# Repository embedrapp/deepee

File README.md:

# DeepEE

DeepEE is a small benchmark for AI agents doing embedded firmware and KiCad engineering. An agent receives a prompt plus starter files, edits a fresh working directory, and submits ordinary source files. An offline verifier checks the result. Conversation quality and screenshots do not count.

## Scope

Version 1.2 has 48 tasks: 12 in each engineering category.

| Category | Task IDs | Topics | Pass gate |
|---|---|---|---|
| Firmware | `deepee-fw-001`–`012` | I²C recovery; SHT3x, BME280, MCP9808, INA219, BMP280, ADS1115, DS18B20, SCD4x, PCA9685, and MAX31855 drivers; Modbus CRC | Protected API + native C tests + PlatformIO build |
| Code repair | `deepee-repair-001`–`012` | Scheduler rollover, ring buffers, ADC scaling, SLIP, MQTT, UTF-8, CBOR, PPP FCS, HTTP chunks, Base64, Modbus CRC, and wrap-safe tick timing | Protected API + native C tests |
| Schematics | `deepee-sch-001`–`012` | Power-input repair, MCP9808, INA219, ADS1115, BMP280, AP2112, USB-C sink, RS-485, CAN, I²C level shifting, microSD, and NE555 | Exact component/pin-net contract + exported netlist + ERC |
| PCB | `deepee-pcb-001`–`012` | nRF24L01, MCP9808, and the same ten researched interface circuits used by the schematic set | Exact footprint/pad/outline contract + fully routed nets + DRC |

The tasks are compact adaptations of real bug reports, open-source boards, official KiCad QA material, and published breakout use cases. Provenance is recorded in each task's `SOURCE.md` and summarized in [docs/TASK_SOURCES.md](docs/TASK_SOURCES.md).

The evaluation contract and its limits are documented in [docs/VALIDATION_MODEL.md](docs/VALIDATION_MODEL.md). Contributions must follow [CONTRIBUTING.md](CONTRIBUTING.md), including the known-good and mutant release gates.

## What is verified

Every task declares public, machine-readable critical requirements. A task score remains binary:

```text
all checks pass -> 1
anything fails  -> 0
```

The primary aggregate is Pass@1: the fraction of tasks passed on an agent's first publishable attempt. Score files also contain each requirement outcome, its engineering layer, leaf evidence, a layer-level score vector, and a stable decision hash. A strong result in one layer cannot mask a failed critical requirement in another.

The verifier checks required parts and pin/pad nets without comparing an entire design to golden geometry. KiCad performs the final ERC/DRC gate. PCB contracts additionally measure declared physical constraints directly from native copper: all named nets use at least 0.25 mm track width, and the USB-C repair constrains routed D+/D− skew to 1.0 mm. The release gate runs a targeted mutant for every critical requirement and must reject all of them.

This is deliberately a KiCad-native benchmark, not a tool-agnostic EDA benchmark. An AI system may be compared if it can produce the required native KiCad 10 artifacts. Altium- or EasyEDA-only outputs are out of scope because silently converting them would weaken the assurance and make the comparison misleading.

Firmware is verified by native behavioral tests and a real target build. Version 1.2 does not claim runtime peripheral, analog, thermal, EMI, or fabrication signoff; those require suitable simulation or hardware-in-the-loop fixtures and are excluded from task claims.

## Lightweight local preparation

No VM, Colima instance, Docker image, KiCad install, or PlatformIO install is needed on the development laptop. The repository checks use Python and a host C compiler only:

```bash
python3 -m venv .venv
. .venv/bin/activate
pip install -e .
make test
```

The Dockerfiles and scripts are deployment material for a later x86_64 Ubuntu EC2 run. They are not started by the commands above.

## EC2 execution

On an Ubuntu 24.04 x86_64 host:

```bash
./scripts/bootstrap-ec2-ubuntu.sh
# Log out and back in once for Docker group membership.
export CODEX_API_KEY='...'
./scripts/run-ec2-baseline.sh --all-tasks
```

For a ChatGPT subscription-authenticated Codex run, complete `codex login --device-auth` on the host and use `./scripts/run-ec2-chatgpt-baseline.sh` instead.

The deployment builds separate `deepee-agent:1.2.0` and `deepee-verifier:1.2.0` images. The agent image has KiCad 10.0.4, PlatformIO 6.1.19, compilers, and Codex but no benchmark tasks or verifier code. Agent runs use an internal-only Docker network and one explicit CONNECT-proxy profile: API-key runs permit `api.openai.com:443`, while ChatGPT-subscription runs additionally permit `auth.openai.com:443` and `chatgpt.com:443`. Both profiles block every other authority and direct internet egress, and the effective profile and allowlist are recorded in the run. Verification runs without any network or agent credentials. Before a baseline starts, the Ubuntu host also proves one private reference submission for every task against that same verifier image. See [docs/EC2.md](docs/EC2.md) and [docs/RUN_PROTOCOL.md](docs/RUN_PROTOCOL.md).

For a manual external agent that uses KiCad:

```bash
deepee benchmark \
  --agent agents/manual-kicad.yaml \
  --task deepee-pcb-001 \
  --prepare-only

deepee verify \
  --container-image deepee-verifier:1.2.0 \
  --task deepee-pcb-001 \
  --run-dir '<printed-run-directory>' \
  --output results/scored/external-pcb-run.json
```

DeepEE's original code and fixtures are MIT licensed. The KiCad-derived schematic starter identified in [THIRD_PARTY_NOTICES.md](THIRD_PARTY_NOTICES.md) retains its GPLv3 license. Compare leaderboard results only when the benchmark and task hashes match.

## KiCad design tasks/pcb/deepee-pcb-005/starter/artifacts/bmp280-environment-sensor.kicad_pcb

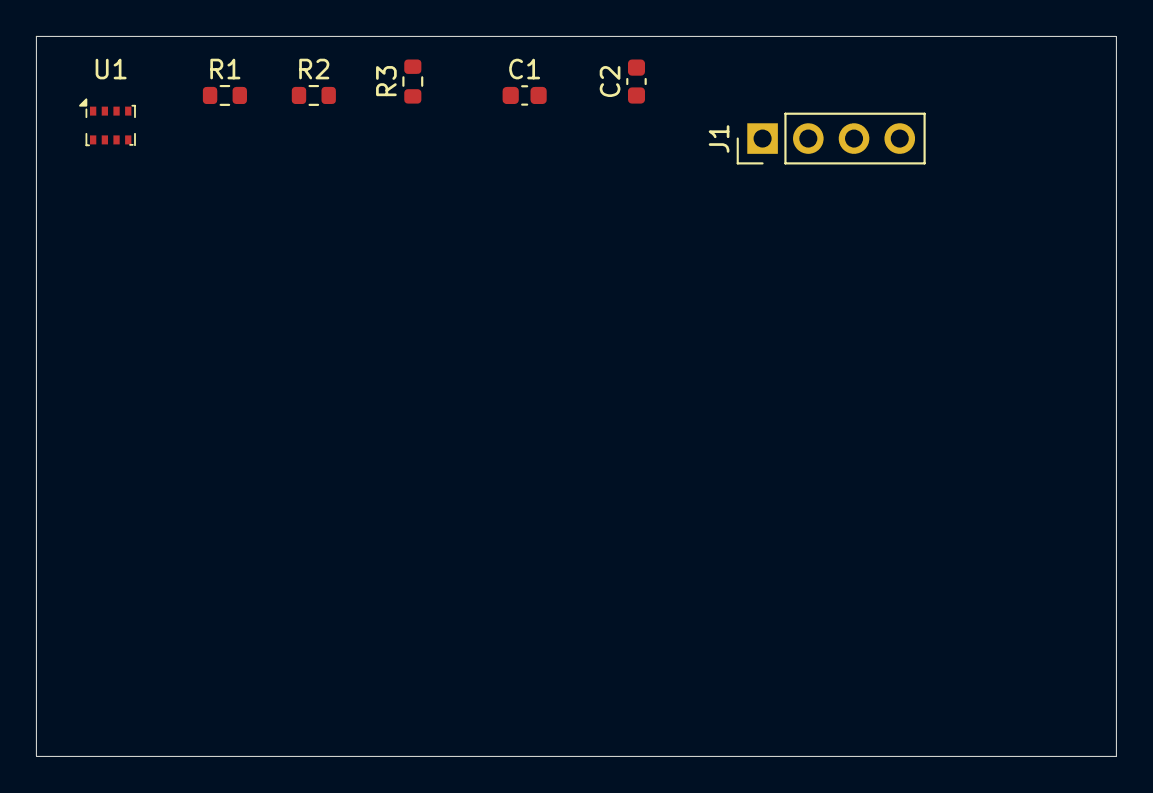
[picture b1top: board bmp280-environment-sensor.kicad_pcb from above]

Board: 2 copper layers, 60.0 x 40.0 mm, 7 parts (0 on the bottom side), 5 nets, no tracks yet.

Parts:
C1: 100nF; C_0603_1608Metric
C2: 1uF; C_0603_1608Metric
J1: Conn_01x04; PinHeader_1x04_P2.54mm_Vertical
R1, R2: 4.7k; R_0603_1608Metric
R3: 0R; R_0603_1608Metric
U1: BMP280; Bosch_LGA-8_2x2.5mm_P0.65mm_ClockwisePinNumbering

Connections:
3V3: C1.1, C2.1, J1.1, R1.1, R2.1, U1.2, U1.6, U1.8
ADDR: R3.1, U1.5
GND: C1.2, C2.2, J1.2, R3.2, U1.1, U1.7
SCL: J1.4, R2.2, U1.4
SDA: J1.3, R1.2, U1.3

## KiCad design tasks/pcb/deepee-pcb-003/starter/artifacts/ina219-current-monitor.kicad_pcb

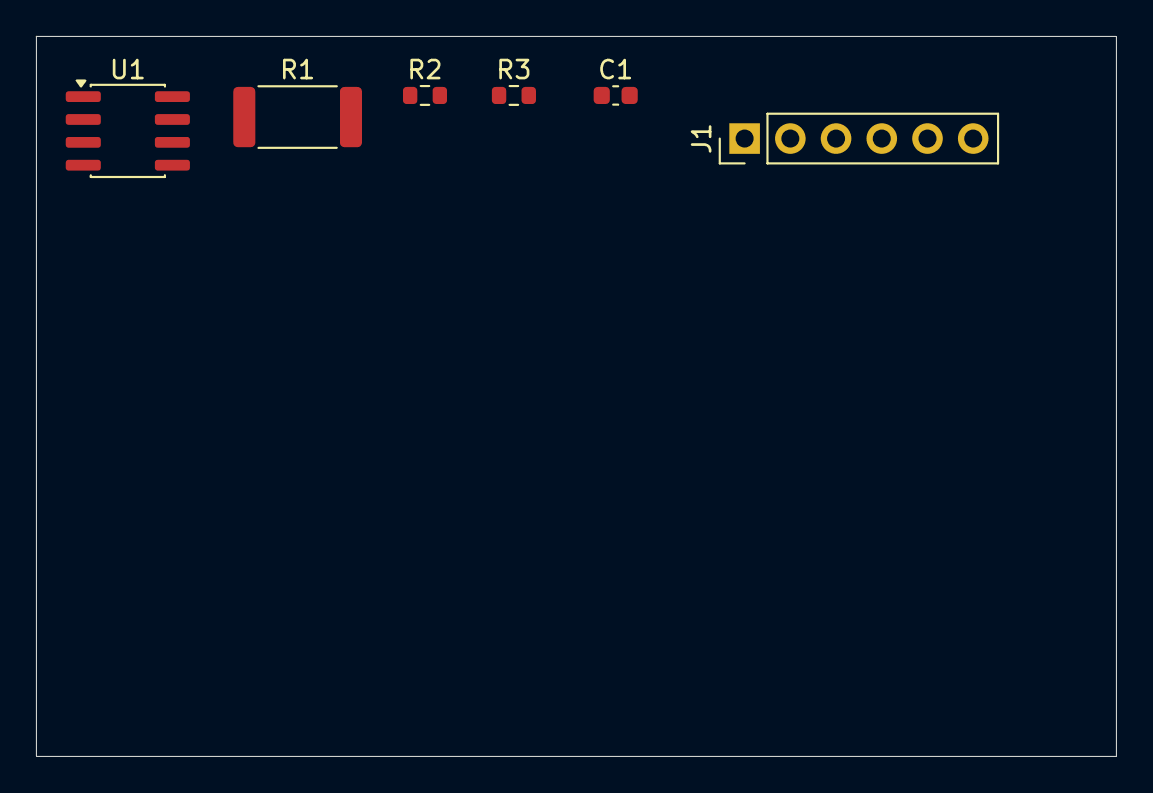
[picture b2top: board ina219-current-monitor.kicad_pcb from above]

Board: 2 copper layers, 60.0 x 40.0 mm, 6 parts (0 on the bottom side), 6 nets, no tracks yet.

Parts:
C1: 100nF; C_0603_1608Metric
J1: Conn_01x06; PinHeader_1x06_P2.54mm_Vertical
R1: 0.1R; R_2512_6332Metric
R2, R3: 4.7k; R_0603_1608Metric
U1: INA219AxD; SOIC-8_3.9x4.9mm_P1.27mm

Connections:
3V3: C1.1, J1.3, R2.1, R3.1, U1.5
GND: C1.2, J1.4, U1.1, U1.2, U1.6
SCL: J1.6, R3.2, U1.4
SDA: J1.5, R2.2, U1.3
VIN_IN: J1.1, R1.1, U1.8
VIN_OUT: J1.2, R1.2, U1.7

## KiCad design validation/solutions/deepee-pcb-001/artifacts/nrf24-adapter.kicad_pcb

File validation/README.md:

# Release validation

This directory contains one known-good submission for every benchmark task plus the validator-adequacy tooling. It is public for reproducibility but used only as a release gate: the validation harness overlays each solution onto a fresh starter and verifies it with the same offline, read-only submission mount used for real scores.

`validation/` is excluded from the Docker build context and is not copied into either benchmark image. It must never be mounted into an agent run. The CI and EC2 release gates run it only after the agent and verifier images have been built. Agent networking is restricted, so an evaluated agent cannot retrieve the public solutions during its run.

The adequacy gate creates one targeted mutant for every critical requirement and requires the mapped oracle to reject it:

```bash
python -m validation.adequacy --container-image deepee-verifier:1.2.0
```

This proves that the validator detects the declared fault. It does not prove that every possible engineering defect has been modeled; task claims must stay within the published requirement contract.

Regenerate the KiCad fixtures only when their task contracts change:

```bash
python -m pip install -r validation/requirements.txt
KICAD_SYMBOL_DIR=/usr/share/kicad/symbols \
  python validation/generate_hardware_fixtures.py

python validation/generate_expanded_code_tasks.py
KICAD_SYMBOL_DIR=/usr/share/kicad/symbols \
  python validation/generate_expanded_hardware_tasks.py

# Run with KiCad's Python runtime to replace the repair-board placeholders
# with placed, net-assigned library footprints.
KICAD_FOOTPRINT_DIR=/usr/share/kicad/footprints \
  python validation/generate_expanded_hardware_tasks.py --pcb-starters-only

# Inside the exact verifier image so pcbnew and the footprint libraries match:
python validation/canonicalize_hardware_boards.py adapter
python validation/canonicalize_hardware_boards.py breakout
```

Validate all reference submissions on the Ubuntu x86_64 benchmark host:

```bash
python -m validation.reference --container-image deepee-verifier:1.2.0
```

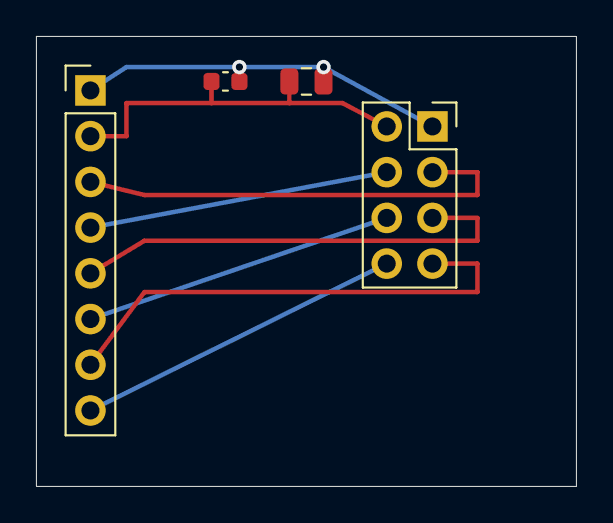
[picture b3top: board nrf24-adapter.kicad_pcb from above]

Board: 2 copper layers, 30.0 x 25.0 mm, 4 parts (0 on the bottom side), 8 nets.

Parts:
C1: 10uF; C_0805_2012Metric
C2: 100nF; C_0603_1608Metric
J1: Conn_01x08; PinHeader_1x08_P2.54mm_Vertical
J2: nRF24L01_Module; PinSocket_2x04_P2.54mm_Vertical

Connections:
+3V3: C1.1, C2.1, J1.2, J2.2
CE: J1.3, J2.3
CSN: J1.4, J2.4
GND: C1.2, C2.2, J1.1, J2.1
IRQ: J1.8, J2.8
MISO: J1.7, J2.7
MOSI: J1.6, J2.6
SCK: J1.5, J2.5

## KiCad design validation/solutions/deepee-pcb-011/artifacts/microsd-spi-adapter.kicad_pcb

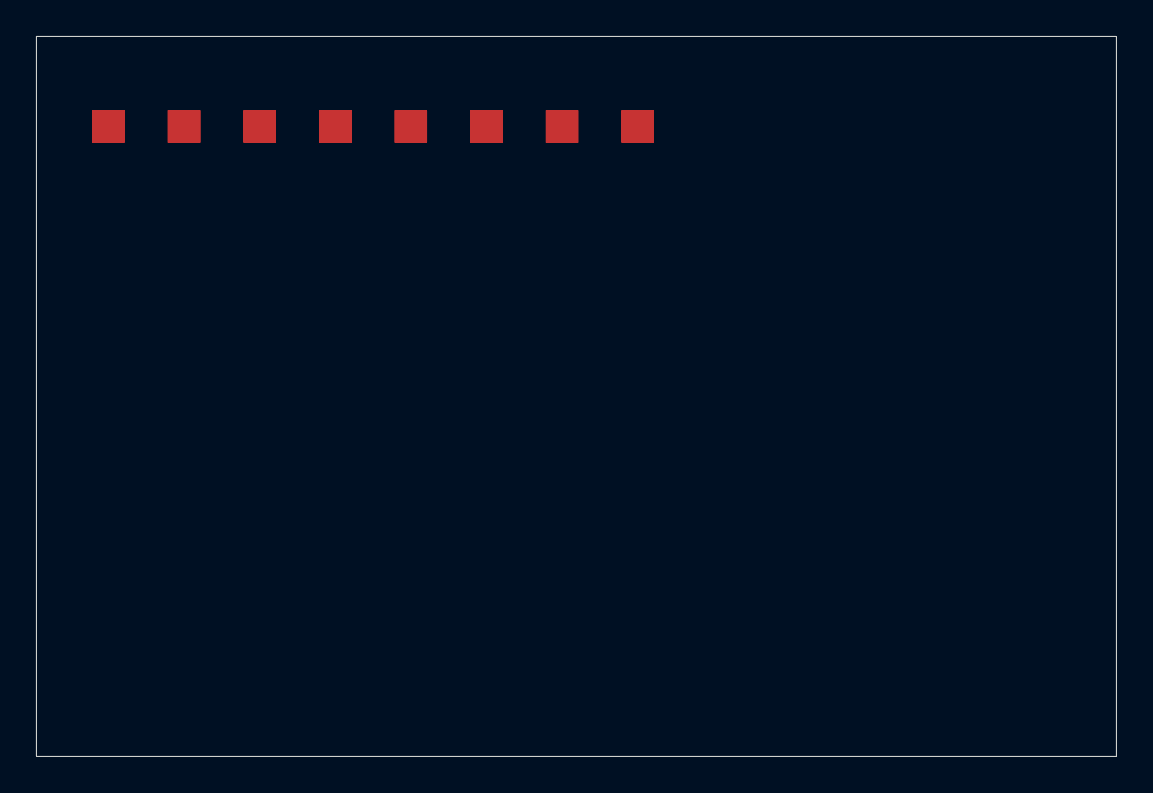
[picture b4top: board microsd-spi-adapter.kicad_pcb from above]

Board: 2 copper layers, 60.0 x 40.0 mm, 7 parts (0 on the bottom side), 8 nets.

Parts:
C1: 100nF; C_0603_1608Metric
C2: 10uF; C_0805_2012Metric
J1: Micro_SD_Card; microSD_HC_Hirose_DM3AT-SF-PEJM5
J2: Conn_01x06; PinHeader_1x06_P2.54mm_Vertical
R1, R2, R3: 47k; R_0603_1608Metric

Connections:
3V3: C1.1, C2.1, J1.4, J2.1, R1.1, R2.1, R3.1
DAT1: J1.8, R2.2
DAT2: J1.1, R3.2
GND: C1.2, C2.2, J1.6, J1.SH, J2.2
MISO: J1.7, J2.5
MOSI: J1.3, J2.4
SCK: J1.5, J2.6
SD_CS: J1.2, J2.3, R1.2

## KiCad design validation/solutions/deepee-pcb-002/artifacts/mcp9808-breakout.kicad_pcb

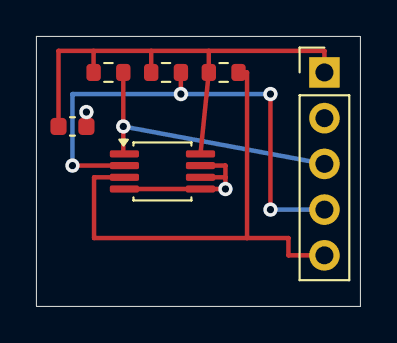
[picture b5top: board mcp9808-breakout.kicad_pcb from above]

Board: 2 copper layers, 18.0 x 15.0 mm, 6 parts (0 on the bottom side), 5 nets.

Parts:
C1: 100nF; C_0603_1608Metric
J1: Conn_01x05; PinHeader_1x05_P2.54mm_Vertical
R1, R2: 4.7k; R_0603_1608Metric
R3: 10k; R_0603_1608Metric
U1: MCP9808T-E/MS; MSOP-8_3x3mm_P0.65mm

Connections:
3V3: C1.1, J1.1, R1.1, R2.1, R3.1, U1.8
ALERT: J1.5, R3.2, U1.3
GND: C1.2, J1.2, U1.4, U1.5, U1.6, U1.7
SCL: J1.4, R2.2, U1.2
SDA: J1.3, R1.2, U1.1

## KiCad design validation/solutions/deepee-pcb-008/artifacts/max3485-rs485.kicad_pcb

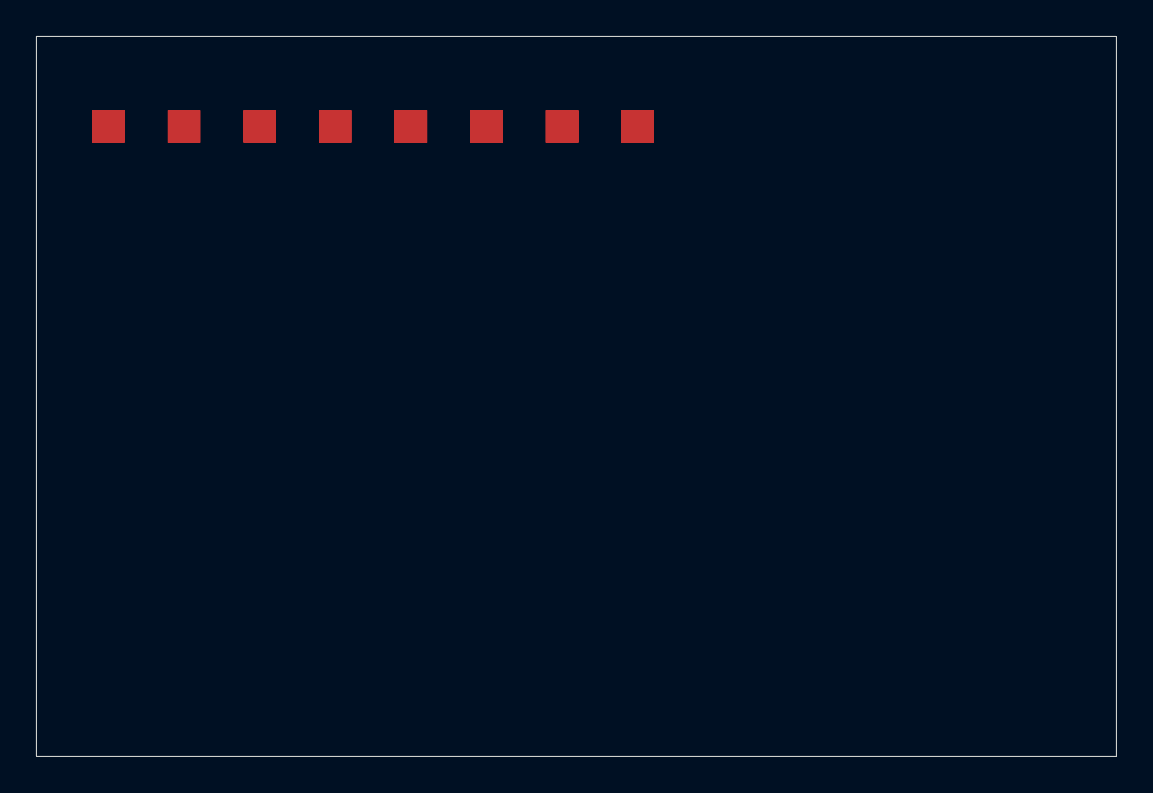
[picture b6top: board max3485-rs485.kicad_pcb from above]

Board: 2 copper layers, 60.0 x 40.0 mm, 7 parts (0 on the bottom side), 8 nets.

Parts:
C1: 100nF; C_0603_1608Metric
J1: Conn_01x06; PinHeader_1x06_P2.54mm_Vertical
J2: Conn_01x03; TerminalBlock_RND_205-00288_1x03_P5.08mm_Horizontal
R1: 120R; R_0603_1608Metric
R2, R3: 680R; R_0603_1608Metric
U1: MAX3485; SOIC-8_3.9x4.9mm_P1.27mm

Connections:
3V3: C1.1, J1.1, R2.1, U1.8
A: J2.1, R1.1, R2.2, U1.6
B: J2.2, R1.2, R3.1, U1.7
DE: J1.5, U1.3
DI: J1.6, U1.4
GND: C1.2, J1.2, J2.3, R3.2, U1.5
RE_N: J1.4, U1.2
RO: J1.3, U1.1

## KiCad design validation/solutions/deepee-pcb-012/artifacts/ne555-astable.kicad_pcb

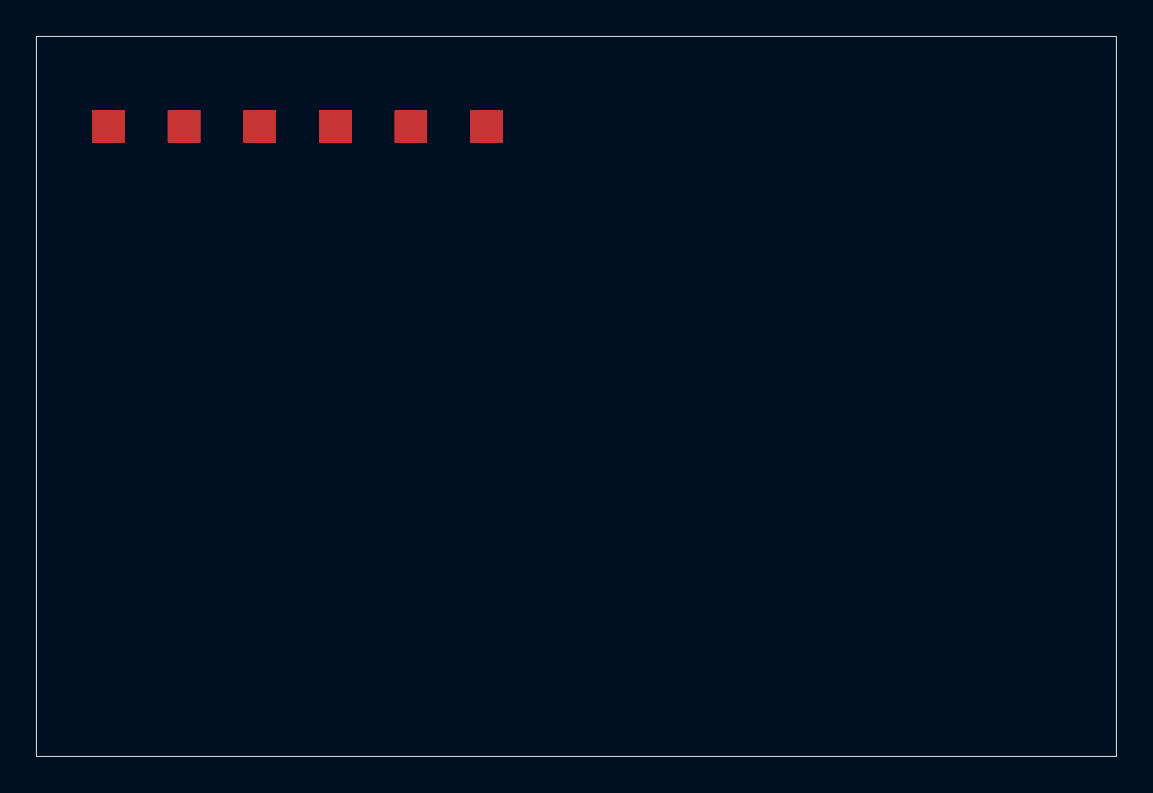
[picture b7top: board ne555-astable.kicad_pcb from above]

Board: 2 copper layers, 60.0 x 40.0 mm, 7 parts (0 on the bottom side), 6 nets.

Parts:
C1, C2: 10nF; C_0603_1608Metric
C3: 100nF; C_0603_1608Metric
J1: Conn_01x03; PinHeader_1x03_P2.54mm_Vertical
R1: 4.7k; R_0603_1608Metric
R2: 68k; R_0603_1608Metric
U1: NE555D; SOIC-8_3.9x4.9mm_P1.27mm

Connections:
5V: C3.1, J1.1, R1.1, U1.4, U1.8
CTRL: C2.1, U1.5
DISCHARGE: R1.2, R2.1, U1.7
GND: C1.2, C2.2, C3.2, J1.2, U1.1
OUT: J1.3, U1.3
TIMING: C1.1, R2.2, U1.2, U1.6

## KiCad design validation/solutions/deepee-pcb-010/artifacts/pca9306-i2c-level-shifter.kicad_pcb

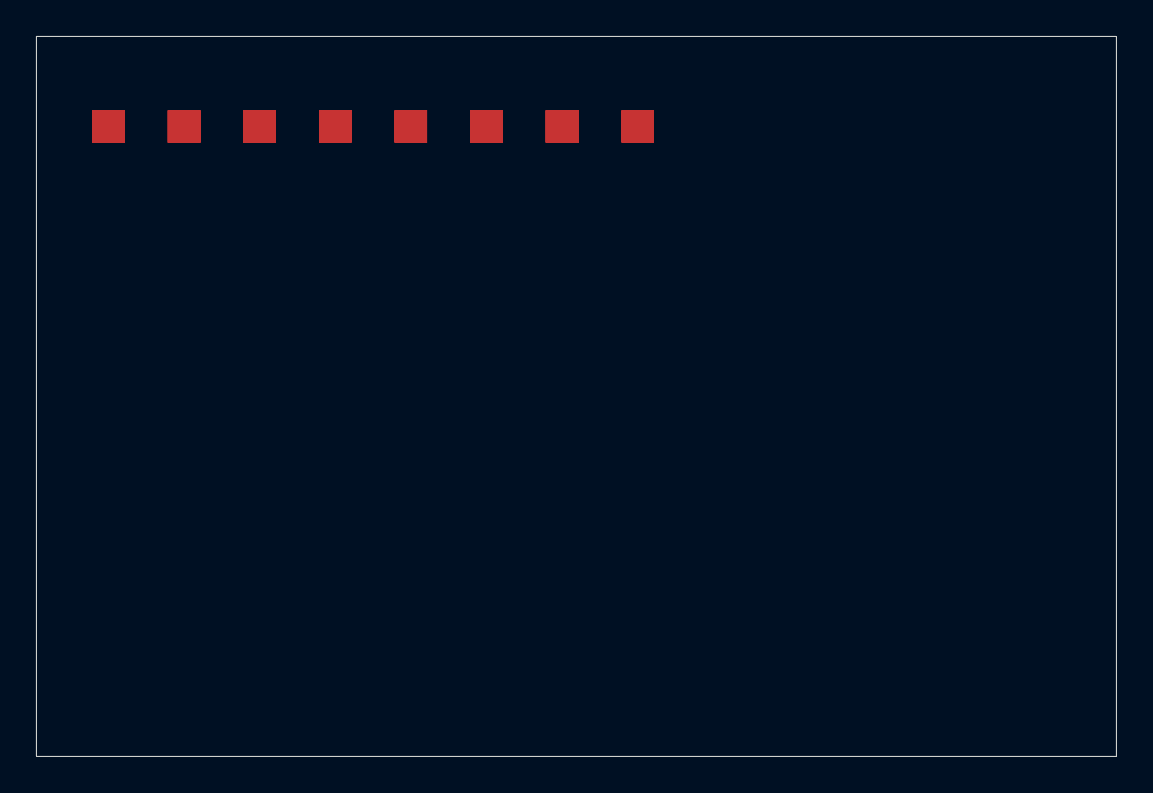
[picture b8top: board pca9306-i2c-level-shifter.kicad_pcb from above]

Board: 2 copper layers, 60.0 x 40.0 mm, 10 parts (0 on the bottom side), 8 nets.

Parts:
C1, C2: 100nF; C_0603_1608Metric
J1, J2: Conn_01x04; PinHeader_1x04_P2.54mm_Vertical
R1, R2, R3, R4: 4.7k; R_0603_1608Metric
R5: 200k; R_0603_1608Metric
U1: PCA9306D; TSSOP-8_3x3mm_P0.65mm

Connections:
1V8: C1.1, J1.1, R1.1, R2.1, U1.2
3V3: C2.1, J2.1, R3.1, R4.1, R5.2, U1.7
ENABLE: R5.1, U1.8
GND: C1.2, C2.2, J1.2, J2.2, U1.1
SCL_1V8: J1.4, R2.2, U1.3
SCL_3V3: J2.4, R4.2, U1.6
SDA_1V8: J1.3, R1.2, U1.4
SDA_3V3: J2.3, R3.2, U1.5

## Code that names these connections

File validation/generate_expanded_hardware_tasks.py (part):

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            c("R2", "4.7k", "Device:R", "Resistor_SMD:R_0603_1608Metric", "3V3", "SDA"),
            c("R3", "4.7k", "Device:R", "Resistor_SMD:R_0603_1608Metric", "3V3", "SCL"),
            c("C1", "100nF", "Device:C", "Capacitor_SMD:C_0603_1608Metric", "3V3", "GND"),
            c("J1", "Conn_01x06", "Connector_Generic:Conn_01x06", "Connector_PinHeader_2.54mm:PinHeader_1x06_P2.54mm_Vertical", "VIN_IN", "VIN_OUT", "3V3", "GND", "SDA", "SCL"),
        ), ("3V3", "GND"),
    ),
    HardwareDesign(
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            c("R2", "4.7k", "Device:R", "Resistor_SMD:R_0603_1608Metric", "3V3", "SCL"),
            c("R3", "10k", "Device:R", "Resistor_SMD:R_0603_1608Metric", "3V3", "ALERT"),
            c("C1", "100nF", "Device:C", "Capacitor_SMD:C_0603_1608Metric", "3V3", "GND"),
            c("J1", "Conn_01x10", "Connector_Generic:Conn_01x10", "Connector_PinHeader_2.54mm:PinHeader_1x10_P2.54mm_Vertical", "3V3", "GND", "SDA", "SCL", "ALERT", "AIN0", "AIN1", "AIN2", "AIN3", "GND"),
        ), ("3V3", "GND"),
    ),
    HardwareDesign(
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            c("R2", "680R", "Device:R", "Resistor_SMD:R_0603_1608Metric", "3V3", "A"),
            c("R3", "680R", "Device:R", "Resistor_SMD:R_0603_1608Metric", "B", "GND"),
            c("C1", "100nF", "Device:C", "Capacitor_SMD:C_0603_1608Metric", "3V3", "GND"),
            c("J1", "Conn_01x06", "Connector_Generic:Conn_01x06", "Connector_PinHeader_2.54mm:PinHeader_1x06_P2.54mm_Vertical", "3V3", "GND", "RO", "RE_N", "DE", "DI"),
            c("J2", "Conn_01x03", "Connector_Generic:Conn_01x03", "TerminalBlock_RND:TerminalBlock_RND_205-00288_1x03_P5.08mm_Horizontal", "A", "B", "GND"),
        ), ("3V3", "GND"),
    ),
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            c("R5", "200k", "Device:R", "Resistor_SMD:R_0603_1608Metric", "ENABLE", "3V3"),
            c("C1", "100nF", "Device:C", "Capacitor_SMD:C_0603_1608Metric", "1V8", "GND"),
            c("C2", "100nF", "Device:C", "Capacitor_SMD:C_0603_1608Metric", "3V3", "GND"),
            c("J1", "Conn_01x04", "Connector_Generic:Conn_01x04", "Connector_PinHeader_2.54mm:PinHeader_1x04_P2.54mm_Vertical", "1V8", "GND", "SDA_1V8", "SCL_1V8"),
            c("J2", "Conn_01x04", "Connector_Generic:Conn_01x04", "Connector_PinHeader_2.54mm:PinHeader_1x04_P2.54mm_Vertical", "3V3", "GND", "SDA_3V3", "SCL_3V3"),
        ), ("1V8", "3V3", "GND"),
    ),
    HardwareDesign(
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            c("R3", "47k", "Device:R", "Resistor_SMD:R_0603_1608Metric", "3V3", "DAT2"),
            c("C1", "100nF", "Device:C", "Capacitor_SMD:C_0603_1608Metric", "3V3", "GND"),
            c("C2", "10uF", "Device:C", "Capacitor_SMD:C_0805_2012Metric", "3V3", "GND"),
            c("J2", "Conn_01x06", "Connector_Generic:Conn_01x06", "Connector_PinHeader_2.54mm:PinHeader_1x06_P2.54mm_Vertical", "3V3", "GND", "SD_CS", "MOSI", "MISO", "SCK"),
        ), ("3V3", "GND"),
    ),
    HardwareDesign(
        12, "ne555-astable", "NE555 astable oscillator",
        "A production fixture needs a roughly 1 kHz free-running oscillator from 5 V, with reset held active, a timing RC network, control-pin bypassing, supply decoupling, and a three-pin output header.",
        ("https://www.ti.com/lit/ds/symlink/ne555.pdf",),
        (
            c("U1", "NE555D", "Timer:NE555D", "Package_SO:SOIC-8_3.9x4.9mm_P1.27mm", "GND", "TIMING", "OUT", "5V", "CTRL", "TIMING", "DISCHARGE", "5V"),
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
